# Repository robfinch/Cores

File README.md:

Cores
=====
RTF's Cores
Use at your own risk.
Welcome to my galaxy of cores.
Contained in the directories are IP cores, source code for digital circuits.
Also included are documentation, test benches, and software samples.

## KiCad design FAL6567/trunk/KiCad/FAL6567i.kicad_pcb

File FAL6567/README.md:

# FAL6567

This set of cores makes up a 6567 VIC-II compatible circuit. The core would be implmented in an FPGA or other PLD and would need additional logic for level translations to substitute into a 6567 socket.

## Features
HDMI output
16 sprites
80 column text mode

## Output
Most modern TV's and monitors support HDMI inputs.

## Sprites
By making use of fast paged mode, FPM, of the dynamic RAM, FAL6567 may support up to 16 sprites.
The additional sprites reuse the existing registers. There is a switch in register 32h which selects which sprite registers are visible.
Register 32h may be used to select legacy sprite operation and the set of sprite registers visible.
When 80 column text mode is active sprites may be positioned at only every other X pixel location. This is a design choice because there are 1040 horizontal positions in 80 column mode requiring 10 bits to represent, but the VIC-II register set has room for only a nine-bit coordinate.

## 80 Column Text
A modern display can easily display 80 columns of text in a crisp clean fashion without blurring or fuzziness.
Because the displayed image is rendered to an internal buffer to convert the image to DVI/HDMI output an 80 column mode is possible without needing to increase the frequency of memory access.
Twice as much memory is scanned for character data, this results in longer badlines.

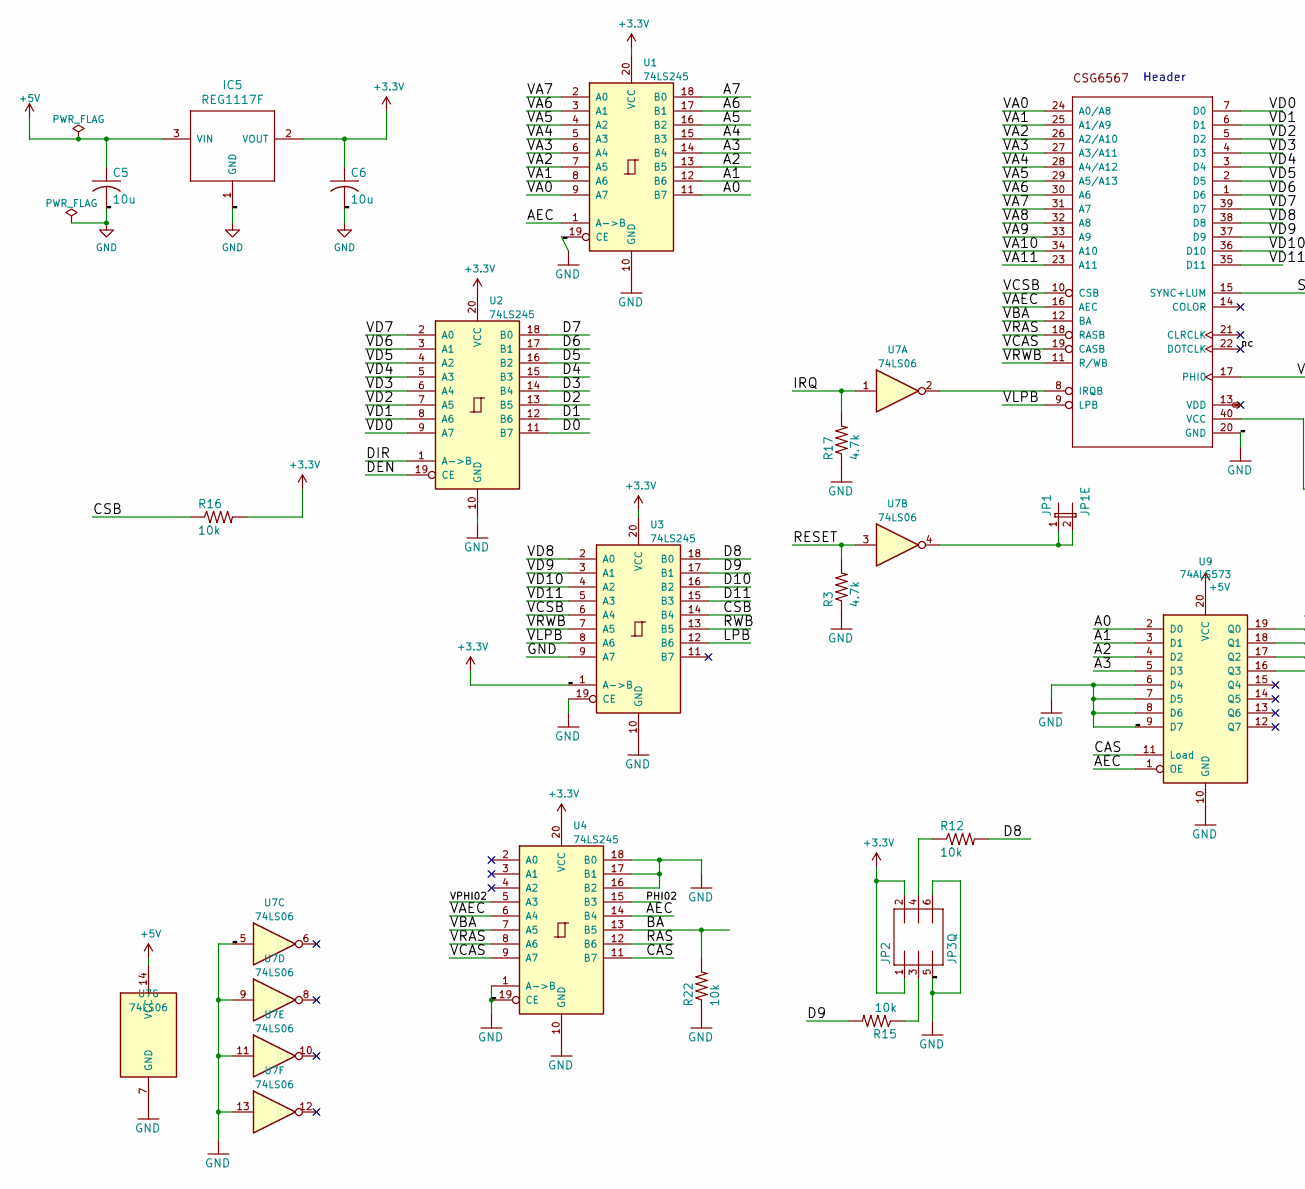
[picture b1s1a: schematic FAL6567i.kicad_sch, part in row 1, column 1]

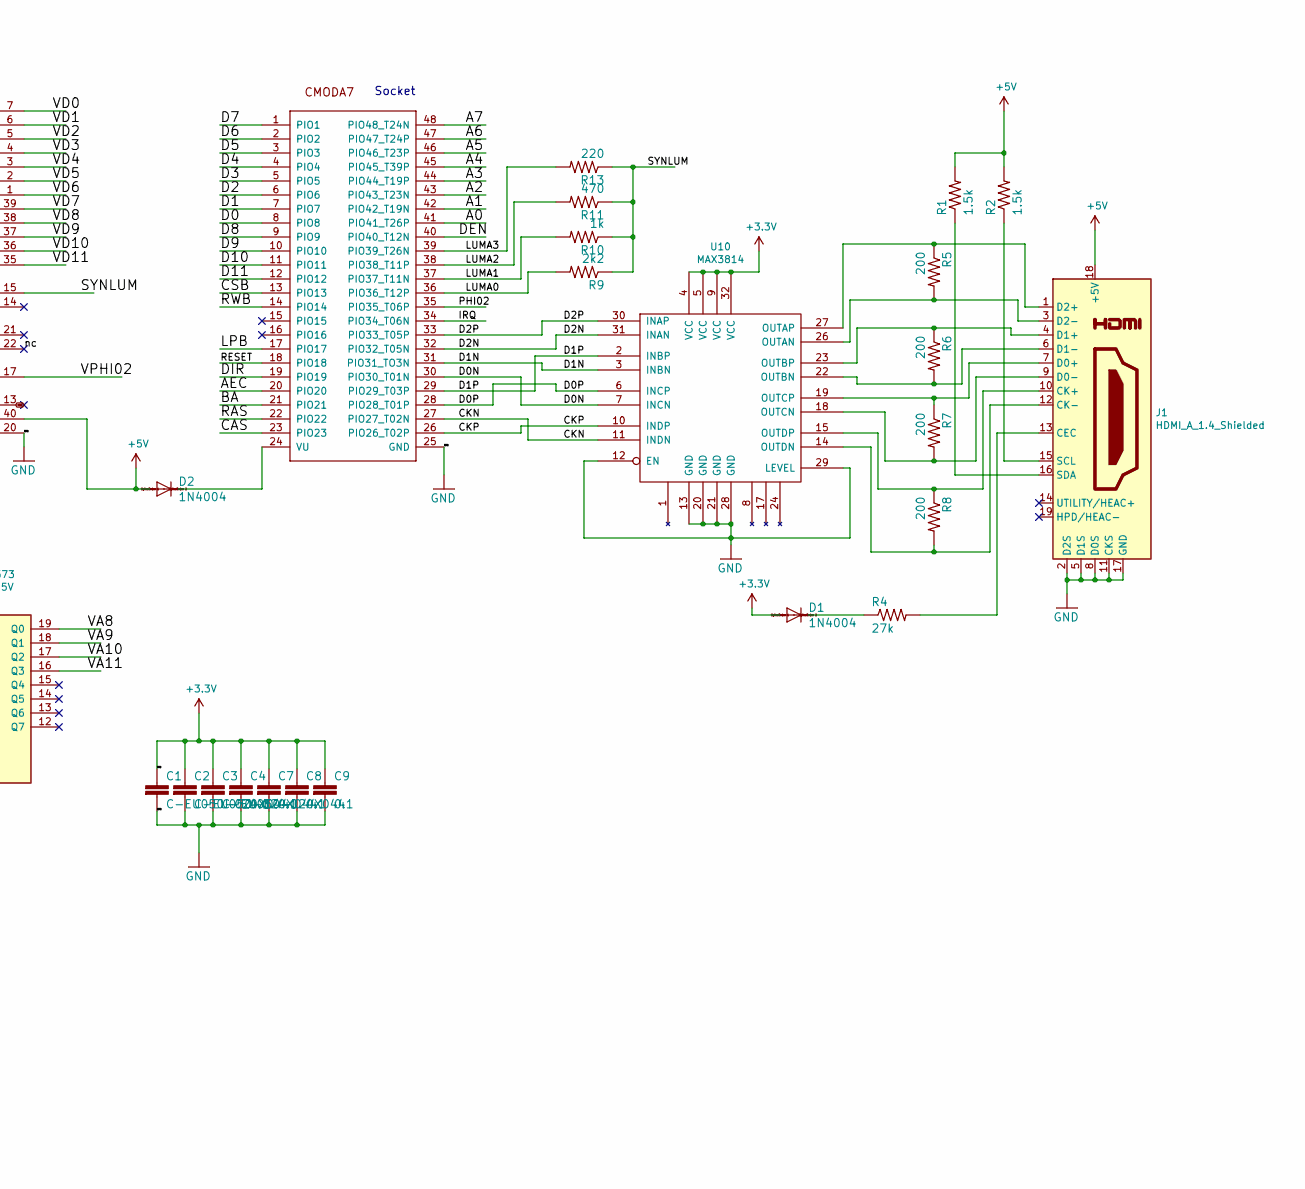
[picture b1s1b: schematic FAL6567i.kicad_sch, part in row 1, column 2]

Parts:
C1, C2, C3: C-EU050-024X044; C050-024X044
C4, C7, C8, C9: 0.1; C050-024X044
C5, C6: 10u; C_Rect_L7.0mm_W6.5mm_P5.00mm
D1, D2: 1N4004; DO41-10
IC5: REG1117F; TO-262-3-1EP_Horizontal_TabDown
J1: HDMI_A_1.4_Shielded; DIP-20_W7.62mm
JP1: JP1E; JP1
JP2: JP3Q
R1, R2: 1.5k; 0204_7
R3, R17: 4.7k; 0204_7
R4: 27k; 0204_7
R5, R6, R7, R8: 200; 0204_7
R9: 2k2; 0204_7
R10: 1k; 0204_7
R11: 470; 0204_7
R12, R15, R16, R22: 10k; 0204_7
R13: 220; 0204_7
U1, U2, U3, U4: 74LS245; DIP-20_W7.62mm
U7: 74LS06; DIP-14_W7.62mm
U9: 74ALS573; DIP-20_W7.62mm
U10: MAX3814; DIP-32_W15.24mm
U$1: CSG6567; DIP-40
U$2: CMODA7; DIL48

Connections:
+3V3: C1.1, C2.1, C3.1, C4.1, C6.1, C7.1, C8.1, C9.1, D1.A, IC5.2 (VOUT), JP2.1, JP2.2, R16.2, U3.1 (A->B), U10.4 (VCC), U10.5 (VCC), U10.9 (VCC), U10.32 (VCC)
+5V: C5.1, D2.A, IC5.3 (VIN), J1.18 (+5V), R1.2, R2.2, U1.20 (VCC), U2.20 (VCC), U3.20 (VCC), U4.20 (VCC), U7.14 (VCC), U9.20 (VCC), U$1.40 (VCC)
/A0: U1.11 (B7), U9.2 (D0), U$2.41 (PIO41_T26P)
/A1: U1.12 (B6), U9.3 (D1), U$2.42 (PIO42_T19N)
/A2: U1.13 (B5), U9.4 (D2), U$2.43 (PIO43_T23N)
/A3: U1.14 (B4), U9.5 (D3), U$2.44 (PIO44_T19P)
/A4: U1.15 (B3), U$2.45 (PIO45_T39P)
/A5: U1.16 (B2), U$2.46 (PIO46_T23P)
/A6: U1.17 (B1), U$2.47 (PIO47_T24P)
/A7: U1.18 (B0), U$2.48 (PIO48_T24N)
/AEC: U1.1 (A->B), U4.14 (B4), U9.1 (OE), U$2.20 (PIO20)
/BA: R22.2, U4.13 (B5), U$2.21 (PIO21)
/CKN: U10.11 (INDN), U$2.27 (PIO27_T02N)
/CKP: U10.10 (INDP), U$2.26 (PIO26_T02P)
/CSB: R16.1, U3.14 (B4), U$2.13 (PIO13)
/D0: U2.11 (B7), U$2.8 (PIO8)
/D0N: U10.7 (INCN), U$2.30 (PIO30_T01N)
/D0P: U10.6 (INCP), U$2.28 (PIO28_T01P)
/D1: U2.12 (B6), U$2.7 (PIO7)
/D1N: U10.3 (INBN), U$2.31 (PIO31_TO3N)
/D1P: U10.2 (INBP), U$2.29 (PIO29_T03P)
/D2: U2.13 (B5), U$2.6 (PIO6)
/D2N: U10.31 (INAN), U$2.32 (PIO32_T05N)
/D2P: U10.30 (INAP), U$2.33 (PIO33_T05P)
/D3: U2.14 (B4), U$2.5 (PIO5)
/D4: U2.15 (B3), U$2.4 (PIO4)
/D5: U2.16 (B2), U$2.3 (PIO3)
/D6: U2.17 (B1), U$2.2 (PIO2)
/D7: U2.18 (B0), U$2.1 (PIO1)
/D8: R12.2, U3.18 (B0), U$2.9 (PIO9)
/D9: R15.2, U3.17 (B1), U$2.10 (PIO10)
/D10: U3.16 (B2), U$2.11 (PIO11)
/D11: U3.15 (B3), U$2.12 (PIO12)
/DEN: U2.19 (CE), U$2.40 (PIO40_T12N)
/DIR: U2.1 (A->B), U$2.19 (PIO19)
/IRQ: R17.2, U7.1, U$2.34 (PIO34_T06N)
/LPB: U3.12 (B6), U$2.17 (PIO17)
/LUMA0: R9.2, U$2.36 (PIO36_T12P)
/LUMA1: R10.2, U$2.37 (PIO37_T11N)
/LUMA2: R11.2, U$2.38 (PIO38_T11P)
/LUMA3: R13.2, U$2.39 (PIO39_T26N)
/PHI02: U4.15 (B3), U$2.35 (PIO35_T06P)
/RESET: R3.2, U7.3, U$2.18 (PIO18)
/RWB: U3.13 (B5), U$2.14 (PIO14)
/SYNLUM: R9.1, R10.1, R11.1, R13.1, U$1.15 (SYNC+LUM)
/VA0: U1.9 (A7), U$1.24 (A0/A8)
/VA1: U1.8 (A6), U$1.25 (A1/A9)
/VA2: U1.7 (A5), U$1.26 (A2/A10)
/VA3: U1.6 (A4), U$1.27 (A3/A11)
/VA4: U1.5 (A3), U$1.28 (A4/A12)
/VA5: U1.4 (A2), U$1.29 (A5/A13)
/VA6: U1.3 (A1), U$1.30 (A6)
/VA7: U1.2 (A0), U$1.31 (A7)
/VA8: U9.19 (Q0), U$1.32 (A8)
/VA9: U9.18 (Q1), U$1.33 (A9)
/VA10: U9.17 (Q2), U$1.34 (A10)
/VA11: U9.16 (Q3), U$1.23 (A11)
/VAEC: U4.6 (A4), U$1.16 (AEC)
/VBA: U4.7 (A5), U$1.12 (BA)
/VCAS: U4.9 (A7), U$1.19 (CASB)
/VCSB: U3.6 (A4), U$1.10 (CSB)
/VD0: U2.9 (A7), U$1.7 (D0)
/VD1: U2.8 (A6), U$1.6 (D1)
/VD2: U2.7 (A5), U$1.5 (D2)
/VD3: U2.6 (A4), U$1.4 (D3)
/VD4: U2.5 (A3), U$1.3 (D4)
/VD5: U2.4 (A2), U$1.2 (D5)
/VD6: U2.3 (A1), U$1.1 (D6)
/VD7: U2.2 (A0), U$1.39 (D7)
/VD8: U3.2 (A0), U$1.38 (D8)
/VD9: U3.3 (A1), U$1.37 (D9)
/VD10: U3.4 (A2), U$1.36 (D10)
/VD11: U3.5 (A3), U$1.35 (D11)
/VLPB: U3.8 (A6), U$1.9 (LPB)
/VPHI02: U4.5 (A3), U$1.17 (PHI0)
/VRAS: U4.8 (A6), U$1.18 (RASB)
/VRWB: U3.7 (A5), U$1.11 (R/WB)
/nc: U$1.22 (DOTCLK)
GND: C1.2, C2.2, C3.2, C4.2, C5.2, C6.2, C7.2, C8.2, C9.2, IC5.1 (GND), J1.2 (D2S), J1.5 (D1S), J1.8 (D0S), J1.11 (CKS), J1.17 (GND), JP2.5, JP2.6, R3.1, R17.1, R22.1, U1.10 (GND), U1.19 (CE), U2.10 (GND), U3.9 (A7), U3.10 (GND), U3.19 (CE), U4.1 (A->B), U4.10 (GND), U4.16 (B2), U4.17 (B1), U4.18 (B0), U4.19 (CE), U7.5, U7.7 (GND), U7.9, U7.11, U7.13, U9.6 (D4), U9.7 (D5), U9.8 (D6), U9.9 (D7), U9.10 (GND), U10.12 (EN), U10.13 (GND), U10.20 (GND), U10.21 (GND), U10.28 (GND), U10.29 (LEVEL), U$1.20 (GND), U$2.25 (GND)
unnamed: D1.C, R4.1
unnamed: D2.C, U$2.24 (VU)
unnamed: J1.1 (D2+), R5.1, U10.27 (OUTAP)
unnamed: J1.3 (D2-), R5.2, U10.26 (OUTAN)
unnamed: J1.4 (D1+), R6.1, U10.23 (OUTBP)
unnamed: J1.6 (D1-), R6.2, U10.22 (OUTBN)
unnamed: J1.7 (D0+), R7.1, U10.19 (OUTCP)
unnamed: J1.9 (D0-), R7.2, U10.18 (OUTCN)
unnamed: J1.10 (CK+), R8.1, U10.15 (OUTDP)
unnamed: J1.12 (CK-), R8.2, U10.14 (OUTDN)
unnamed: J1.13 (CEC), R4.2
unnamed: J1.15 (SCL), R2.1
unnamed: J1.16 (SDA), R1.1
unnamed: JP1.1, JP1.2, U7.4
unnamed: JP2.3, R15.1
unnamed: JP2.4, R12.1
unnamed: U7.2, U$1.8 (IRQB)
VDD: U$1.13 (VDD)

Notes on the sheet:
Header
Socket

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
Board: 2 copper layers, 41 parts (0 on the bottom side), 97 nets, no tracks yet.

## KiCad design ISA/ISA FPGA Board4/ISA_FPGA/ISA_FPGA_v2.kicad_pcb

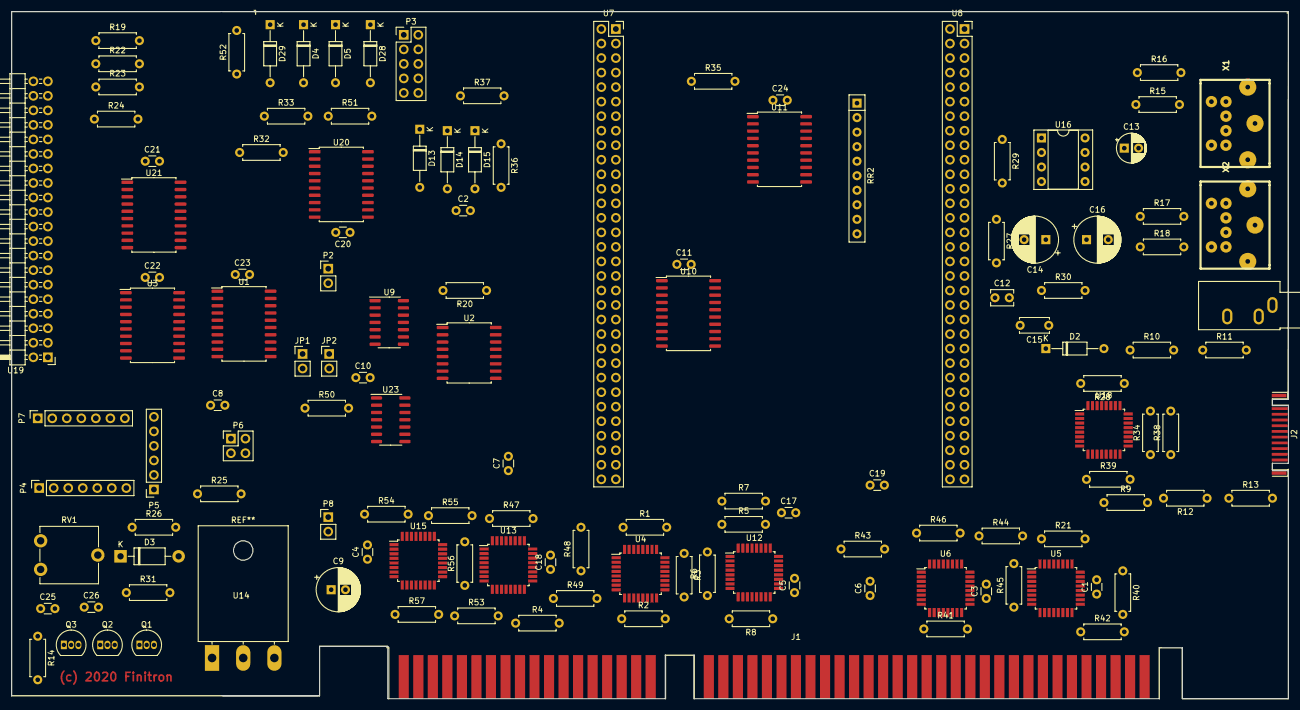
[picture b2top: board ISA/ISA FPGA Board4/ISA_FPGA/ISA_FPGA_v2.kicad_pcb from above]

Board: 4 copper layers, 223.3 x 120.1 mm, 132 parts (0 on the bottom side), 246 nets, no tracks yet.

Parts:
C1, C2, C3, C4, C5, C6, C7, C8, C10, C11, C17, C18, C19, C20, C21, C22, C23, C24: 0.1; C_Disc_D3.0mm_W1.6mm_P2.50mm
C9: 10uF; CP_Radial_D7.5mm_P2.50mm
C12: 0.047u; C_Disc_D3.8mm_W2.6mm_P2.50mm
C13: 10u; CP_Radial_D5.0mm_P2.50mm
C14: 100u; CP_Radial_D8.0mm_P3.80mm
C15: 0.047u; C_Disc_D5.0mm_W2.5mm_P5.00mm
C16: 220u; CP_Radial_D8.0mm_P3.80mm
C25, C26: 0.01; C_Disc_D3.0mm_W1.6mm_P2.50mm
D2, D13, D14, D15: ZPDxx; D_DO-35_SOD27_P10.16mm_Horizontal
D3: 1N750; D_DO-41_SOD81_P10.16mm_Horizontal
D4, D5, D28, D29: LED; D_DO-35_SOD27_P10.16mm_Horizontal
J1: Bus_ISA_16bit; BUS_AT
J2: HDMI_A; HDMI_A_Contact_Technology_HDMI-19APL2_Horizontal
J3: AudioJack2; Jack_3.5mm_CUI_SJ1-3533NG_Horizontal
JP1, JP2: Jumper; PinHeader_1x02_P2.54mm_Vertical
P2, P8: CONN_2; PinHeader_1x02_P2.54mm_Vertical
P3: CONN_5X2; PinHeader_2x05_P2.54mm_Vertical
P4, P7: CONN_7; PinSocket_1x07_P2.54mm_Vertical
P5: CONN_6; PinSocket_1x06_P2.54mm_Vertical
P6: CONN_2X2; PinHeader_2x02_P2.54mm_Vertical
Q1, Q2, Q3: 2N3904; TO-92_Inline
R1, R2, R3, R4, R5, R6, R7, R8, R15, R16, R17, R18, R21, R28, R34, R38, R39, R40, R41, R42, R43, R44, R45, R46, R47, R48, R49, R53, R54, R55, R56, R57: 200; R_Axial_DIN0207_L6.3mm_D2.5mm_P7.62mm_Horizontal
R9, R19, R22, R23: 10k; R_Axial_DIN0207_L6.3mm_D2.5mm_P7.62mm_Horizontal
R10: 27k; R_Axial_DIN0207_L6.3mm_D2.5mm_P7.62mm_Horizontal
R11, R12: 1k5; R_Axial_DIN0207_L6.3mm_D2.5mm_P7.62mm_Horizontal
R13: 100k; R_Axial_DIN0207_L6.3mm_D2.5mm_P7.62mm_Horizontal
R14: 4k7; R_Axial_DIN0207_L6.3mm_D2.5mm_P7.62mm_Horizontal
R20: 2k2; R_Axial_DIN0207_L6.3mm_D2.5mm_P7.62mm_Horizontal
R24: 0; R_Axial_DIN0207_L6.3mm_D2.5mm_P7.62mm_Horizontal
R25: 1M; R_Axial_DIN0207_L6.3mm_D2.5mm_P7.62mm_Horizontal
R26, R31: 1k; R_Axial_DIN0207_L6.3mm_D2.5mm_P7.62mm_Horizontal
R27, R29: 5k1; R_Axial_DIN0207_L6.3mm_D2.5mm_P7.62mm_Horizontal
R30: 10; R_Axial_DIN0207_L6.3mm_D2.5mm_P7.62mm_Horizontal
R32, R33: 470; R_Axial_DIN0207_L6.3mm_D2.5mm_P7.62mm_Horizontal
R35, R36, R37, R51, R52: 100; R_Axial_DIN0207_L6.3mm_D2.5mm_P7.62mm_Horizontal
R50: 10K; R_Axial_DIN0207_L6.3mm_D2.5mm_P7.62mm_Horizontal
RR2: 10k; R_Array_SIP10
RV1: 10k; Potentiometer_ACP_CA9-V10_Vertical
U1, U3: 74LS573; SOIC-20W_7.5x12.8mm_P1.27mm
U2: 74LVC138; SOIC-16W_7.5x10.3mm_P1.27mm
U4, U5, U6, U12, U13, U15, U18: MAX3814; TQFP-32_7x7mm_P0.8mm
U7, U8: CONN_32X2; PinSocket_2x32_P2.54mm_Vertical
U9: 74LVC06; SOIC-14_3.9x8.7mm_P1.27mm
U10, U11, U21: 74LVC245; SOIC-20W_7.5x12.8mm_P1.27mm
U14: LM3940; LMxx
U16: LM386; DIP-8_W7.62mm_Socket
U19: CONN_20X2; PinHeader_2x20_P2.54mm_Horizontal
U20: 74LVC573; SOIC-20W_7.5x12.8mm_P1.27mm
U23: 74LVC14; SOIC-14_3.9x8.7mm_P1.27mm
X1, X2: MINI_DIN_6; PS2

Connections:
/ANA0: R35.2, U8.15
/ANA1: R36.2, U7.30
/ANA2: R37.2, U7.29
/AUD: C12.1, R27.2, U7.52
/CLK: JP2.1, U23.6
/CS1FX*: RR2.3, U11.16, U19.37
/CS3FX*: RR2.4, U11.15, U19.38
/CSEL: R24.1, U19.28
/DA0: U2.3, U19.35, U20.19
/DA1: U19.33, U20.18
/DA2: U19.36, U20.17
/DBEN*: U7.19, U21.19
/DD0: U1.2, U3.19, U19.17, U21.18
/DD1: U1.3, U3.18, U19.15, U21.17
/DD2: U1.4, U3.17, U19.13, U21.16
/DD3: U1.5, U3.16, U19.11, U21.15
/DD4: U1.6, U3.15, U19.9, U21.14
/DD5: U1.7, U3.14, U19.7, U21.13
/DD6: U1.8, U3.13, U19.5, U21.12
/DD7: R19.1, U1.9, U3.12, U19.3, U21.11
/DD8: U1.19, U3.2, U19.4
/DD9: U1.18, U3.3, U19.6
/DD10: U1.17, U3.4, U19.8
/DD11: U1.16, U3.5, U19.10
/DD12: U1.15, U3.6, U19.12
/DD13: U1.14, U3.7, U19.14
/DD14: U1.13, U3.8, U19.16
/DD15: U1.12, U3.9, U19.18
/DDIR: U7.17, U21.1
/DIOR*: RR2.2, U11.17, U19.25
/DIOW*: RR2.1, U11.18, U19.23
/DMARQ: R22.1, U10.11, U19.21
/EN138: U2.6, U7.28
/FAD0: U7.24, U20.2, U21.2
/FAD1: U7.22, U20.3, U21.3
/FAD2: U7.20, U20.4, U21.4
/FAD3: U7.18, U21.5
/FAD4: U7.16, U21.6
/FAD5: U7.12, U21.7
/FAD6: U7.10, U21.8
/FAD7: U7.8, U21.9
/FALE: U7.26, U20.11
/FBEN: U4.12, U5.12, U6.12, U11.19, U23.10
/FBENN: U8.18, U23.11
/FCLK: U8.7, U23.5
/FCS1FX*: U7.11, U11.4
/FCS3FX*: U7.13, U11.5
/FDIORN: U2.2, U7.9, U11.3
/FDIOWN: U2.1, U7.7, U11.2
/FMRQ0: U8.9, U10.8
/FMRQ1: U8.11, U10.7
/FMRQ2: U8.13, U10.6
/FMRQ3: U7.23, U10.5
/FMRQ5: U7.25, U10.4
/FMRQ6: U7.27, U10.3
/FMRQ7: U8.17, U10.2
/FMS0: U8.45, U11.7
/FMS1: U8.47, U11.8
/FMS2: U8.49, U11.9
/FOSC: U8.48, U23.9
/FRCLK0N: R5.2, U8.43, U12.26
/FRCLK0P: R5.1, U8.44, U12.27
/FRDAT0N: R6.2, U8.41, U12.22
/FRDAT0P: R6.1, U8.42, U12.23
/FRDAT1N: R7.2, U8.29, U12.18
/FRDAT1P: R7.1, U8.30, U12.19
/FRDAT2N: R8.2, U8.33, U12.14
/FRDAT2P: R8.1, U8.34, U12.15
/FRDAT3N: R47.2, U8.27, U13.26
/FRDAT3P: R47.1, U8.28, U13.27
/FRDAT4N: R48.2, U8.23, U13.22
/FRDAT4P: R48.1, U8.24, U13.23
/FRDAT5N: R49.2, U8.21, U13.18
/FRDAT5P: R49.1, U8.22, U13.19
/FRDAT6N: R53.2, U8.19, U13.14
/FRDAT6P: R53.1, U8.20, U13.15
/FRDAT7N: R54.2, U8.25, U15.26
/FRDAT7P: R54.1, U8.26, U15.27
/FRDAT8N: R55.2, U8.35, U15.22
/FRDAT8P: R55.1, U8.36, U15.23
/FRDAT9N: R56.2, U8.31, U15.18
/FRDAT9P: R56.1, U8.32, U15.19
/FRDAT10N: R57.2, U8.37, U15.14
/FRDAT10P: R57.1, U8.38, U15.15
/FRX: R50.1, U8.56
/FTCLK0N: U4.31, U7.41
/FTCLK0P: U4.30, U7.42
/FTDAT0N: U4.3, U7.39
/FTDAT0P: U4.2, U7.40
/FTDAT1N: U4.7, U7.45
/FTDAT1P: U4.6, U7.46
/FTDAT2N: U4.11, U7.53
/FTDAT2P: U4.10, U7.54
/FTDAT3N: U5.31, U7.31
/FTDAT3P: U5.30, U7.32
/FTDAT4N: U5.3, U7.35
/FTDAT4P: U5.2, U7.36
/FTDAT5N: U5.7, U7.37
/FTDAT5P: U5.6, U7.38
/FTDAT6N: U5.11, U7.43
/FTDAT6P: U5.10, U7.44
/FTDAT7N: U6.31, U7.55
/FTDAT7P: U6.30, U7.56
/FTDAT8N: U6.3, U7.49
/FTDAT8P: U6.2, U7.50
/FTDAT9N: U6.7, U7.57
/FTDAT9P: U6.6, U7.58
/FTDAT10N: U6.11, U7.59
/FTDAT10P: U6.10, U7.60
/FTX: P6.3, U8.55
/HCLKN: U8.59, U18.11
/HCLKP: U8.60, U18.10
/HD0N: U8.57, U18.7
/HD0P: U8.58, U18.6
/HD1N: U8.51, U18.3
/HD1P: U8.52, U18.2
/HD2N: U8.53, U18.31
/HD2P: U8.54, U18.30
/INTRQ: U7.15, U19.31
/KBDCLK: R15.1, U8.10
/KBDDAT: R16.1, U8.8
/LED0: R51.1, U8.40
/LED1: R52.1, U8.39
/MRQ0: J1.71, U10.12
/MRQ1: J1.18, U10.13
/MRQ2: J1.6, U10.14
/MRQ3: J1.16, U10.15
/MRQ5: J1.73, U10.16
/MRQ6: J1.75, U10.17
/MRQ7: J1.77, U10.18
/MS0: J1.11, RR2.5, U11.13
/MS1: J1.12, RR2.6, U11.12
/MS2: J1.13, RR2.7, U11.11
/MSECLK: R18.1, U8.16
/MSEDAT: R17.1, U8.12
/OSC: JP1.1, U23.8
/PU1: RR2.8, RR2.9, RR2.10, U3.11, U9.10
/R0CLKN: J1.58, U12.31
/R0CLKP: J1.57, U12.30
/R0DAT0N: J1.60, U12.3
/R0DAT0P: J1.59, U12.2
/R0DAT1N: J1.62, U12.7
/R0DAT1P: J1.61, U12.6
/R0DAT2N: J1.82, U12.11
/R0DAT2P: J1.81, U12.10
/R0DAT3N: J1.84, U13.31
/R0DAT3P: J1.83, U13.30
/R0DAT4N: J1.86, U13.3
/R0DAT4P: J1.85, U13.2
/R0DAT5N: J1.88, U13.7
/R0DAT5P: J1.87, U13.6
/R0DAT6N: J1.90, U13.11
/R0DAT6P: J1.89, U13.10
/R0DAT7N: J1.92, U15.31
/R0DAT7P: J1.91, U15.30
/R0DAT8N: J1.94, U15.3
/R0DAT8P: J1.93, U15.2
/R0DAT9N: J1.96, U15.7
/R0DAT9P: J1.95, U15.6
/R0DAT10N: J1.98, U15.11
/R0DAT10P: J1.97, U15.10
/RAND: U7.34, U23.2, U23.3
/RDY: R20.1, U9.1, U9.6, U19.27
/RDY*: U8.14, U9.5
/RESET: J1.2, U9.3
/RESET*: U7.21, U9.4, U19.1
/T0CLKN: J1.55, R1.2, U4.26
/T0CLKP: J1.56, R1.1, U4.27
/T0DAT0N: J1.53, R2.2, U4.22
/T0DAT0P: J1.54, R2.1, U4.23
/T0DAT1N: J1.51, R3.2, U4.18
/T0DAT1P: J1.52, R3.1, U4.19
/T0DAT2N: J1.49, R4.2, U4.14
/T0DAT2P: J1.50, R4.1, U4.15
/T0DAT3N: J1.47, R21.2, U5.26
/T0DAT3P: J1.48, R21.1, U5.27
/T0DAT4N: J1.45, R40.2, U5.22
/T0DAT4P: J1.46, R40.1, U5.23
/T0DAT5N: J1.43, R41.2, U5.18
/T0DAT5P: J1.44, R41.1, U5.19
/T0DAT6N: J1.41, R42.2, U5.14
/T0DAT6P: J1.42, R42.1, U5.15
/T0DAT7N: J1.39, R43.2, U6.26
/T0DAT7P: J1.40, R43.1, U6.27
/T0DAT8N: J1.37, R44.2, U6.22
/T0DAT8P: J1.38, R44.1, U6.23
/T0DAT9N: J1.35, R45.2, U6.18
/T0DAT9P: J1.36, R45.1, U6.19
/T0DAT10N: J1.33, R46.2, U6.14
/T0DAT10P: J1.34, R46.1, U6.15
/VCC12: C14.1, C25.1, J1.9, R14.1, R25.1, R26.1, U16.6
/VCC33: C1.1, C2.1, C3.1, C4.1, C5.1, C6.1, C7.1, C9.1, C10.1, C11.1, C17.1, C18.1, C19.1, C20.1, C21.1, C22.1, C23.1, C24.1, D2.2, U1.20, U2.16, U3.20, U4.4, U4.5, U4.9, U4.32, U5.4, U5.5, U5.9, U5.32, U6.4, U6.5, U6.9, U6.32, U9.14, U10.20, U11.1, U11.20, U12.4, U12.5, U12.9, U12.32, U13.4, U13.5, U13.9, U13.32, U14.VO, U15.4, U15.5, U15.9, U15.32, U18.4, U18.5, U18.9, U18.32, U20.20, U21.20, U23.14, X1.5, X2.5
/VCC_CF: P2.2, U19.20
GND: C1.2, C2.2, C3.2, C4.2, C5.2, C6.2, C7.2, C9.2, C10.2, C11.2, C12.2, C14.2, C15.2, C17.2, C18.2, C19.2, C20.2, C21.2, C22.2, C23.2, C24.2, C25.2, D3.2, D4.2, D13.2, D14.2, D15.2, D28.2, D29.2, J1.1, J1.10, J1.14, J1.15, J1.17, J1.26, J1.27, J1.28, J1.31, J1.63, J1.64, J1.70, J1.72, J1.74, J1.76, J1.79, J1.80, J2.2, J2.5, J2.8, J2.11, J2.17, J3.S, P3.1, P3.3, P3.5, P3.7, P3.9, P5.1, P7.7, Q2.1, Q3.1, R9.2, R13.2, R19.2, R22.2, R23.2, R24.2, R29.1, R31.2, U1.10, U2.4, U2.5, U2.8, U3.10, U4.13, U4.20, U4.21, U4.28, U5.13, U5.20, U5.21, U5.28, U6.13, U6.20, U6.21, U6.28, U7.1, U7.2, U7.5, U7.6, U7.61, U7.62, U8.5, U8.6, U8.61, U8.62, U9.7, U9.9, U9.13, U10.1, U10.10, U10.19, U11.10, U12.12, U12.13, U12.20, U12.21, U12.28, U13.12, U13.13, U13.20, U13.21, U13.28, U14.GND, U15.12, U15.13, U15.20, U15.21, U15.28, U16.2, U16.4, U18.13, U18.20, U18.21, U18.28, U19.2, U19.19, U19.22, U19.24, U19.26, U19.30, U19.40, U20.1, U20.10, U21.10, U23.7
unnamed: C8.1, P5.6
unnamed: C13.1, U16.1
unnamed: C13.2, U16.8
unnamed: C15.1, R30.1
unnamed: C16.1, R30.2, U16.5
unnamed: C16.2, J3.T
unnamed: C26.1, Q1.1, Q2.3, R14.2
unnamed: C26.2, Q3.2, R25.2
unnamed: D2.1, R10.1
unnamed: D3.1, Q3.3, RV1.2, U23.1
unnamed: D4.1, R32.2
unnamed: D5.2, R33.2
unnamed: D13.1, P3.10, R37.1
unnamed: D14.1, P3.6, R36.1
unnamed: D15.1, P3.2, R35.1
unnamed: D28.1, R51.2
unnamed: D29.1, R52.2
unnamed: J1.20, JP2.2
unnamed: J1.30, JP1.2
unnamed: J2.1, R28.2, U18.27
unnamed: J2.3, R28.1, U18.26
unnamed: J2.4, R34.2, U18.23
unnamed: J2.6, R34.1, U18.22
unnamed: J2.7, R38.2, U18.19
unnamed: J2.9, R38.1, U18.18
unnamed: J2.10, R39.2, U18.15
unnamed: J2.12, R39.1, U18.14
unnamed: J2.13, R10.2
unnamed: J2.15, R12.2
unnamed: J2.16, R11.2
unnamed: J2.19, R13.1
unnamed: P5.3, P7.6, P8.2
unnamed: P5.4, P6.4
unnamed: P5.5, P6.2
unnamed: P6.1, R50.2
unnamed: Q1.2, Q2.2
unnamed: R9.1, U18.12
unnamed: R15.2, X1.6, X1.8
unnamed: R16.2, X1.1, X1.2
unnamed: R17.2, X2.1, X2.2
unnamed: R18.2, X2.6, X2.8
unnamed: R26.2, RV1.3
unnamed: R27.1, R29.2, U16.3
unnamed: R31.1, RV1.1
unnamed: R32.1, R33.1, U23.4
unnamed: U1.1, U2.13
unnamed: U1.11, U23.12
unnamed: U2.9, U23.13
unnamed: U2.10, U3.1
unnamed: U2.14, U9.11
unnamed: X1.3, X2.3
VCC: D5.1, J1.3, J1.29, J1.78, J2.18, P2.1, P8.1, R11.1, R12.1, R20.2, U7.63, U7.64, U8.63, U8.64, U14.VI

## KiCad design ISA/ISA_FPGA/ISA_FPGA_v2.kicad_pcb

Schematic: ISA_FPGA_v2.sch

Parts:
C1, C2, C3, C4, C5, C6, C7, C8, C10, C11, C17, C18, C19, C20, C21, C22, C23, C24: 0.1; C_Disc_D3.0mm_W1.6mm_P2.50mm
C9: 10uF; CP_Radial_D7.5mm_P2.50mm
C12: 0.047u; C_Disc_D3.8mm_W2.6mm_P2.50mm
C13: 10u; CP_Radial_D5.0mm_P2.50mm
C14: 100u; CP_Radial_D8.0mm_P3.80mm
C15: 0.047u; C_Disc_D5.0mm_W2.5mm_P5.00mm
C16: 220u; CP_Radial_D8.0mm_P3.80mm
D1, D28, D29, D30, D31: LED; D_DO-35_SOD27_P10.16mm_Horizontal
D2, D13, D14, D15: ZPDxx; D_DO-35_SOD27_P10.16mm_Horizontal
J1: Bus_ISA_16bit; BUS_AT
J2: HDMI_A; HDMI_Micro-D_Molex_46765-0x01
J3: AudioJack2; Jack_3.5mm_CUI_SJ1-3533NG_Horizontal
JP1, JP2: Jumper; PinHeader_1x02_P2.54mm_Vertical
P2, P8: CONN_2; PinHeader_1x02_P2.54mm_Vertical
P3: CONN_5X2; PinHeader_2x05_P2.54mm_Vertical
P4, P7: CONN_7; PinSocket_1x07_P2.54mm_Vertical
P5: CONN_6; PinSocket_1x06_P2.54mm_Vertical
P6: CONN_2X2; PinHeader_2x02_P2.54mm_Vertical
R1, R2, R3, R4, R5, R6, R7, R8, R15, R16, R17, R18: 200; R_Axial_DIN0207_L6.3mm_D2.5mm_P7.62mm_Horizontal
R9, R19, R22, R23, R24: 10k; R_Axial_DIN0207_L6.3mm_D2.5mm_P7.62mm_Horizontal
R10: 27k; R_Axial_DIN0207_L6.3mm_D2.5mm_P7.62mm_Horizontal
R11, R12: 1k5; R_Axial_DIN0207_L6.3mm_D2.5mm_P7.62mm_Horizontal
R13: 100k; R_Axial_DIN0207_L6.3mm_D2.5mm_P7.62mm_Horizontal
R20, R21: 2k2; R_Axial_DIN0207_L6.3mm_D2.5mm_P7.62mm_Horizontal
R27, R29: 5k1; R_Axial_DIN0207_L6.3mm_D2.5mm_P7.62mm_Horizontal
R28, R35, R36, R37, R51, R52, R53, R54: 100; R_Axial_DIN0207_L6.3mm_D2.5mm_P7.62mm_Horizontal
R30: 10; R_Axial_DIN0207_L6.3mm_D2.5mm_P7.62mm_Horizontal
R50: 10K; R_Axial_DIN0207_L6.3mm_D2.5mm_P7.62mm_Horizontal
RR1: 10k; R_Array_SIP10
U1, U2, U3, U5, U6, U10, U21, U22: 74LVC245; SOIC-20W_7.5x12.8mm_P1.27mm
U4, U12, U18: MAX3814; TQFP-32_7x7mm_P0.8mm
U7, U8: CONN_32X2; PinSocket_2x32_P2.54mm_Vertical
U9: 74LVC06; SOIC-14_3.9x8.7mm_P1.27mm
U11: 74LVC244; SOIC-20W_7.5x12.8mm_P1.27mm
U13: CONN_6x2; PinHeader_2x06_P2.54mm_Vertical
U14: LM3940; LMxx
U15: 74LVC138; SOIC-16W_7.5x10.3mm_P1.27mm
U16: LM386; DIP-8_W7.62mm_Socket
U17: 74LVC574; SOIC-20W_7.5x12.8mm_P1.27mm
U19: CONN_20X2; PinHeader_2x20_P2.54mm_Horizontal
U20: 74LVC573; SOIC-20W_7.5x12.8mm_P1.27mm
X1, X2: MINI_DIN_6; PS2

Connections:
/8M18Hz: JP2.1, U3.8 (A6)
/14M318Hz: JP1.1, U3.9 (A7)
/328_RESET*: C8.2
/AD0: J1.40 (DB0), U5.2 (A0)
/AD1: J1.39 (DB1), U5.3 (A1)
/AD2: J1.38 (DB2), U5.4 (A2)
/AD3: J1.37 (DB3), U5.5 (A3)
/AD4: J1.36 (DB4), U5.6 (A4)
/AD5: J1.35 (DB5), U5.7 (A5)
/AD6: J1.34 (DB6), U5.8 (A6)
/AD7: J1.33 (DB7), U5.9 (A7)
/AD8: J1.91 (D8), U6.9 (A7)
/AD9: J1.92 (D9), U6.8 (A6)
/AD10: J1.93 (D10), U6.7 (A5)
/AD11: J1.94 (D11), U6.6 (A4)
/AD12: J1.95 (D12), U6.5 (A3)
/AD13: J1.96 (D13), U6.4 (A2)
/AD14: J1.97 (D14), U6.3 (A1)
/AD15: J1.98 (D15), U6.2 (A0)
/AD16: J1.62 (BA00), U1.2 (A0)
/AD17: J1.61 (BA01), U1.3 (A1)
/AD18: J1.60 (BA02), U1.4 (A2)
/AD19: J1.59 (BA03), U1.5 (A3)
/AD20: J1.58 (BA04), U1.6 (A4)
/AD21: J1.57 (BA05), U1.7 (A5)
/AD22: J1.56 (BA06), U1.8 (A6)
/AD23: J1.55 (BA07), U1.9 (A7)
/AD24: J1.54 (BA08), U2.2 (A0)
/AD25: J1.53 (BA09), U2.3 (A1)
/AD26: J1.52 (BA10), U2.4 (A2)
/AD27: J1.51 (BA11), U2.5 (A3)
/AD28: J1.50 (BA12), U2.6 (A4)
/AD29: J1.49 (BA13), U2.7 (A5)
/AD30: J1.48 (BA14), U2.8 (A6)
/AD31: J1.47 (BA15), U2.9 (A7)
/ALE: J1.28 (ALE), U3.6 (A4), U17.11 (Cp)
/ANA0: R35.2, U8.15
/ANA1: R36.2, U7.30
/ANA2: R37.2, U7.29
/AUD: C12.1, R27.2, U7.52
/CFG0: RR1.2, U13.1
/CFG1: RR1.3, U13.3
/CFG2: RR1.4, U13.5
/CFG3: RR1.5, U13.7
/CFG4: RR1.6, U13.9
/CLK0N: J1.87 (LA18), R1.2, U4.26
/CLK0P: J1.88 (LA17), R1.1, U4.27
/CS1FX*: U11.14 (O2a), U19.37
/CS3FX*: U11.12 (O3a), U19.38
/CSEL: R24.1, U19.28
/DA0: U19.35, U20.19 (Q0)
/DA1: U19.33, U20.18 (Q1)
/DA2: U19.36, U20.17 (Q2)
/DASP*: U19.39
/DAT0N: J1.85 (LA20), R2.2, U4.22
/DAT0P: J1.86 (LA19), R2.1, U4.23
/DAT1N: J1.83 (LA22), R3.2, U4.18
/DAT1P: J1.84 (LA21), R3.1, U4.19
/DAT2N: J1.81 (SBHE), R4.2, U4.14
/DAT2P: J1.82 (LA23), R4.1, U4.15
/DBEN*: U7.19, U21.19 (CE), U22.19 (CE)
/DD0: U19.17, U21.18 (B0)
/DD1: U19.15, U21.17 (B1)
/DD2: U19.13, U21.16 (B2)
/DD3: U19.11, U21.15 (B3)
/DD4: U19.9, U21.14 (B4)
/DD5: U19.7, U21.13 (B5)
/DD6: U19.5, U21.12 (B6)
/DD7: R19.1, U19.3, U21.11 (B7)
/DD8: U19.4, U22.18 (B0)
/DD9: U19.6, U22.17 (B1)
/DD10: U19.8, U22.16 (B2)
/DD11: U19.10, U22.15 (B3)
/DD12: U19.12, U22.14 (B4)
/DD13: U19.14, U22.13 (B5)
/DD14: U19.16, U22.12 (B6)
/DD15: U19.18, U22.11 (B7)
/DDIR: U7.17, U21.1 (A->B), U22.1 (A->B)
/DDMARQ: U7.41, U10.9 (A7)
/DIOR*: U11.16 (O1a), U19.25
/DIORDY: R23.1, U9.11, U19.27
/DIOW*: U11.18 (O0a), U19.23
/DMACK*: U19.29
/DMARQ: R22.1, U10.11 (B7), U19.21
/DRDY*: U7.15, U9.10
/F8M18Hz: U3.12 (B6), U7.37
/F14M318Hz: U3.11 (B7), U7.39
/FAD0: U5.18 (B0), U7.24, U20.2 (D0), U21.2 (A0)
/FAD1: U5.17 (B1), U7.22, U20.3 (D1), U21.3 (A1)
/FAD2: U5.16 (B2), U7.20, U20.4 (D2), U21.4 (A2)
/FAD3: U5.15 (B3), U7.18, U21.5 (A3)
/FAD4: U5.14 (B4), U7.16, U21.6 (A4)
/FAD5: U5.13 (B5), U7.12, U21.7 (A5)
/FAD6: U5.12 (B6), U7.10, U21.8 (A6)
/FAD7: U5.11 (B7), U7.8, U21.9 (A7)
/FAD8: U6.11 (B7), U7.42, U22.2 (A0)
/FAD9: U6.12 (B6), U7.40, U22.3 (A1)
/FAD10: U6.13 (B5), U7.38, U22.4 (A2)
/FAD11: U6.14 (B4), U7.36, U22.5 (A3)
/FAD12: U6.15 (B3), U7.34, U22.6 (A4)
/FAD13: U6.16 (B2), U7.32, U22.7 (A5)
/FAD14: U6.17 (B1), U7.28, U22.8 (A6)
/FAD15: U6.18 (B0), U7.26, U22.9 (A7)
/FAD16: U1.18 (B0), U8.7
/FAD17: U1.17 (B1), U8.9
/FAD18: U1.16 (B2), U8.11
/FAD19: U1.15 (B3), U8.13
/FAD20: U1.14 (B4), U8.14
/FAD21: U1.13 (B5), U8.17
/FAD22: U1.12 (B6), U8.19
/FAD23: U1.11 (B7), U8.21
/FAD24: U2.18 (B0), U8.23
/FAD25: U2.17 (B1), U8.25
/FAD26: U2.16 (B2), U8.27
/FAD27: U2.15 (B3), U8.29
/FAD28: U2.14 (B4), U8.31
/FAD29: U2.13 (B5), U8.33
/FAD30: U2.12 (B6), U8.35
/FAD31: U2.11 (B7), U8.37
/FALE: U3.14 (B4), U8.18, U20.11 (Load)
/FBDIR: U1.1 (A->B), U2.1 (A->B), U5.1 (A->B), U6.1 (A->B), U8.24
/FBEN: U1.19 (CE), U2.19 (CE), U3.19 (CE), U4.12, U5.19 (CE), U6.19 (CE), U8.39, U11.1 (OEa)
/FCDIR: U3.1 (A->B), U8.32
/FCS1FX*: U7.11, U11.6 (I2a)
/FCS3FX*: U7.13, U11.8 (I3a)
/FDIOR*: U7.9, U11.4 (I1a)
/FDIOW*: U7.7, U11.2 (I0a)
/FINT: U7.48, U9.12
/FINTA: U8.26, U11.11 (I0b)
/FIRQ10: U7.35
/FMRQ0: U7.43, U10.8 (A6)
/FMRQ1: U7.45, U10.7 (A5)
/FMRQ2: U7.53, U10.6 (A4)
/FMRQ3: U7.23, U10.5 (A3)
/FMRQ5: U7.25, U10.4 (A2)
/FMRQ6: U7.27, U10.3 (A1)
/FMRQ7: U7.31, U10.2 (A0)
/FRCLK0N: R5.2, U12.26
/FRCLK0P: R5.1, U12.27
/FRCLKN: U8.55
/FRCLKP: U8.56
/FRD: U3.13 (B5), U8.20
/FRDAT0N: R6.2, U8.49, U12.22
/FRDAT0P: R6.1, U8.50, U12.23
/FRDAT1N: R7.2, U8.47, U12.18
/FRDAT1P: R7.1, U8.48, U12.19
/FRDAT2N: R8.2, U8.45, U12.14
/FRDAT2P: R8.1, U8.46, U12.15
/FRDY*: U8.41, U9.2
/FRX: R50.1, U8.30
/FSEL0: U3.15 (B3), U8.34
/FSEL1: U3.16 (B2), U8.36
/FSEL2: U3.17 (B1), U8.38
/FSEL3: U3.18 (B0), U8.40
/FTCLK0N: U4.31, U7.55
/FTCLK0P: U4.30, U7.56
/FTDAT0N: U4.3, U7.59
/FTDAT0P: U4.2, U7.60
/FTDAT1N: U4.7, U7.57
/FTDAT1P: U4.6, U7.58
/FTDAT2N: U4.11, U7.49
/FTDAT2P: U4.10, U7.50
/FTX: P6.3, U8.28
/HCLKN: U8.59, U18.11
/HCLKP: U8.60, U18.10
/HD0N: U8.57, U18.7
/HD0P: U8.58, U18.6
/HD1N: U8.51, U18.3
/HD1P: U8.52, U18.2
/HD2N: U8.53, U18.31
/HD2P: U8.54, U18.30
/INT*: J1.19 (~REFRESH), U9.13
/INTA: J1.25 (IRQ3), U11.9 (O0b)
/INTRQ: U19.31
/IOCS16*: U19.32
/IRQ: U9.9
/IRQ2: J1.4 (IRQ2)
/IRQ*: R21.1, U9.8
/KBDCLK: R15.1, U8.10
/KBDDAT: R16.1, U8.8
/LED0: R51.1, U7.44
/LED1: R52.1, U7.46
/LED2: R53.1, U7.54
/LED3: R54.1
/LED4: R28.1, U15.15 (O0), U17.2 (D0)
/MAK0*: J1.70 (~DACK0), U17.19 (Q0)
/MAK1*: J1.23 (IRQ5), U17.18 (Q1)
/MAK2*: J1.26 (~DACK2), U17.17 (Q2)
/MAK3*: J1.21 (IRQ7), U17.16 (Q3)
/MAK5*: J1.72 (~DACK5), U17.15 (Q4)
/MAK6*: J1.74 (~DACK6), U17.14 (Q5)
/MAK7*: J1.76 (~DACK7), U17.13 (Q6)
/MOE*: RR1.7, U13.11, U17.1 (OE)
/MRQ0: J1.71 (DRQ0), U10.12 (B6)
/MRQ1: J1.24 (IRQ4), U10.13 (B5)
/MRQ2: J1.6 (DRQ2), U10.14 (B4)
/MRQ3: J1.22 (IRQ6), U10.15 (B3)
/MRQ5: J1.73 (DRQ5), U10.16 (B2)
/MRQ6: J1.75 (DRQ6), U10.17 (B1)
/MRQ7: J1.77 (DRQ7), U10.18 (B0)
/MS0: U8.44, U15.1 (A0)
/MS1: U8.42, U15.2 (A1)
/MS2: U8.43, U15.3 (A2)
/MSECLK: R18.1, U8.16
/MSEDAT: R17.1, U8.12
/PDIAG: U19.34
/RCLK0N: J1.17 (~DACK1), U12.31
/RCLK0P: J1.18 (DRQ1), U12.30
/RD: J1.90 (~MEMW), U3.7 (A5)
/RDAT0N: J1.15 (~DACK3), U12.3
/RDAT0P: J1.16 (DRQ3), U12.2
/RDAT1N: J1.13 (~IOW), U12.7
/RDAT1P: J1.14 (~IOR), U12.6
/RDAT2N: J1.11 (~SMEMW), U12.11
/RDAT2P: J1.12 (~SMEMR), U12.10
/RDY: J1.41 (IO_READY), R20.1, U9.1, U9.6
/RDY*: U8.22, U9.5
/RESET: J1.2 (RESET), U9.3
/RESET*: U7.21, U9.4, U19.1
/SEL0: J1.46 (BA16), U3.5 (A3)
/SEL1: J1.45 (BA17), U3.4 (A2)
/SEL2: J1.44 (BA18), U3.3 (A1)
/SEL3: J1.43 (BA19), U3.2 (A0)
/VCC12: C14.1, J1.9 (+12V), U16.6 (V+)
/VCC33: C1.1, C2.1, C3.1, C4.1, C5.1, C6.1, C7.1, C9.1, C10.1, C11.1, C17.1, C18.1, C19.1, C20.1, C21.1, C22.1, C23.1, C24.1, D2.2 (A), RR1.1 (COM), U1.20 (VCC), U2.20 (VCC), U3.20 (VCC), U4.4, U4.5, U4.9, U4.32, U5.20 (VCC), U6.20 (VCC), U9.14 (VCC), U10.20 (VCC), U11.19 (OEb), U12.4, U12.5, U12.9, U12.32, U14.VO, U15.6 (E3), U15.16 (VCC), U17.20 (VCC), U18.4, U18.5, U18.9, U18.32, U20.20 (VCC), U21.20 (VCC), U22.20 (VCC), X1.5, X2.5
/VCC_CF: P2.2 (PM), U19.20
GND: C1.2, C2.2, C3.2, C4.2, C5.2, C6.2, C7.2, C9.2, C10.2, C11.2, C12.2, C14.2, C15.2, C17.2, C18.2, C19.2, C20.2, C21.2, C22.2, C23.2, C24.2, D1.2 (K), D13.2 (A), D14.2 (A), D15.2 (A), D28.2 (K), D29.2 (K), D30.2 (K), D31.2 (K), J1.1 (GND), J1.10 (GND), J1.31 (GND), J1.80 (GND), J2.2 (D2S), J2.5 (D1S), J2.8 (D0S), J2.11 (CKS), J2.17 (GND), J3.S, P3.1, P3.3, P3.5, P3.7, P3.9, P5.1, P7.7, R9.2, R13.2, R19.2, R22.2, R23.2, R24.2, R29.1, U1.10 (GND), U2.10 (GND), U3.10 (GND), U4.13, U4.20, U4.21, U4.28, U5.10 (GND), U6.10 (GND), U7.1, U7.2, U7.5, U7.6, U7.61, U7.62, U8.5, U8.6, U8.61, U8.62, U9.7 (GND), U10.1 (A->B), U10.10 (GND), U10.19 (CE), U11.10 (GND), U12.12, U12.13, U12.20, U12.21, U12.28, U13.2, U13.4, U13.6, U13.8, U13.10, U13.12, U14.GND, U15.4 (E1), U15.5 (E2), U15.8 (GND), U16.2 (-), U16.4 (GND), U17.10 (GND), U18.13, U18.20, U18.21, U18.28, U19.2, U19.19, U19.22, U19.24, U19.26, U19.30, U19.40, U20.1 (OE), U20.10 (GND), U21.10 (GND), U22.10 (GND)
unnamed: C8.1, P5.6
unnamed: C13.1, U16.1 (GAIN)
unnamed: C13.2, U16.8 (GAIN)
unnamed: C15.1, R30.1
unnamed: C16.1, R30.2, U16.5
unnamed: C16.2, J3.T
unnamed: D1.1 (A), R28.2
unnamed: D2.1 (K), R10.1
unnamed: D13.1 (K), P3.10, R37.1
unnamed: D14.1 (K), P3.6, R36.1
unnamed: D15.1 (K), P3.2, R35.1
unnamed: D28.1 (A), R51.2
unnamed: D29.1 (A), R52.2
unnamed: D30.1 (A), R53.2
unnamed: D31.1 (A), R54.2
unnamed: J1.20 (CLK), JP2.2
unnamed: J1.30 (OSC), JP1.2
unnamed: J2.1 (D2+), U18.27
unnamed: J2.3 (D2-), U18.26
unnamed: J2.4 (D1+), U18.23
unnamed: J2.6 (D1-), U18.22
unnamed: J2.7 (D0+), U18.19
unnamed: J2.9 (D0-), U18.18
unnamed: J2.10 (CK+), U18.15
unnamed: J2.12 (CK-), U18.14
unnamed: J2.13 (CEC), R10.2
unnamed: J2.15 (SCL), R12.2
unnamed: J2.16 (SDA), R11.2
unnamed: J2.19 (HPD), R13.1
unnamed: P5.3, P7.6, P8.2 (PM)
unnamed: P5.4, P6.4
unnamed: P5.5, P6.2
unnamed: P6.1, R50.2
unnamed: R9.1, U18.12
unnamed: R15.2, X1.6, X1.8
unnamed: R16.2, X1.1, X1.2
unnamed: R17.2, X2.1, X2.2
unnamed: R18.2, X2.6, X2.8
unnamed: R27.1, R29.2, U16.3 (+)
unnamed: U15.7 (O7), U17.9 (D7)
unnamed: U15.9 (O6), U17.8 (D6)
unnamed: U15.10 (O5), U17.7 (D5)
unnamed: U15.11 (O4), U17.6 (D4)
unnamed: U15.12 (O3), U17.5 (D3)
unnamed: U15.13 (O2), U17.4 (D2)
unnamed: U15.14 (O1), U17.3 (D1)
unnamed: X1.3, X2.3
VCC: J1.3 (+5V), J1.29 (VCC), J1.78 (+5V), J2.18 (+5V), P2.1, P8.1, R11.1, R12.1, R20.2, R21.2, U7.63, U7.64, U8.63, U8.64, U14.VI

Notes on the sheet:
SparkFun FT231x Serial->USB
Normally Open (USB supplies 5V)
Analog
VREF

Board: 4 copper layers, 105 parts (0 on the bottom side), 263 nets, no tracks yet.

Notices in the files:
ISA/ISA FPGA Board4/ISA_FPGA/ISA_FPGA_v2.kicad_pcb:
(c) 2020 Finitron
